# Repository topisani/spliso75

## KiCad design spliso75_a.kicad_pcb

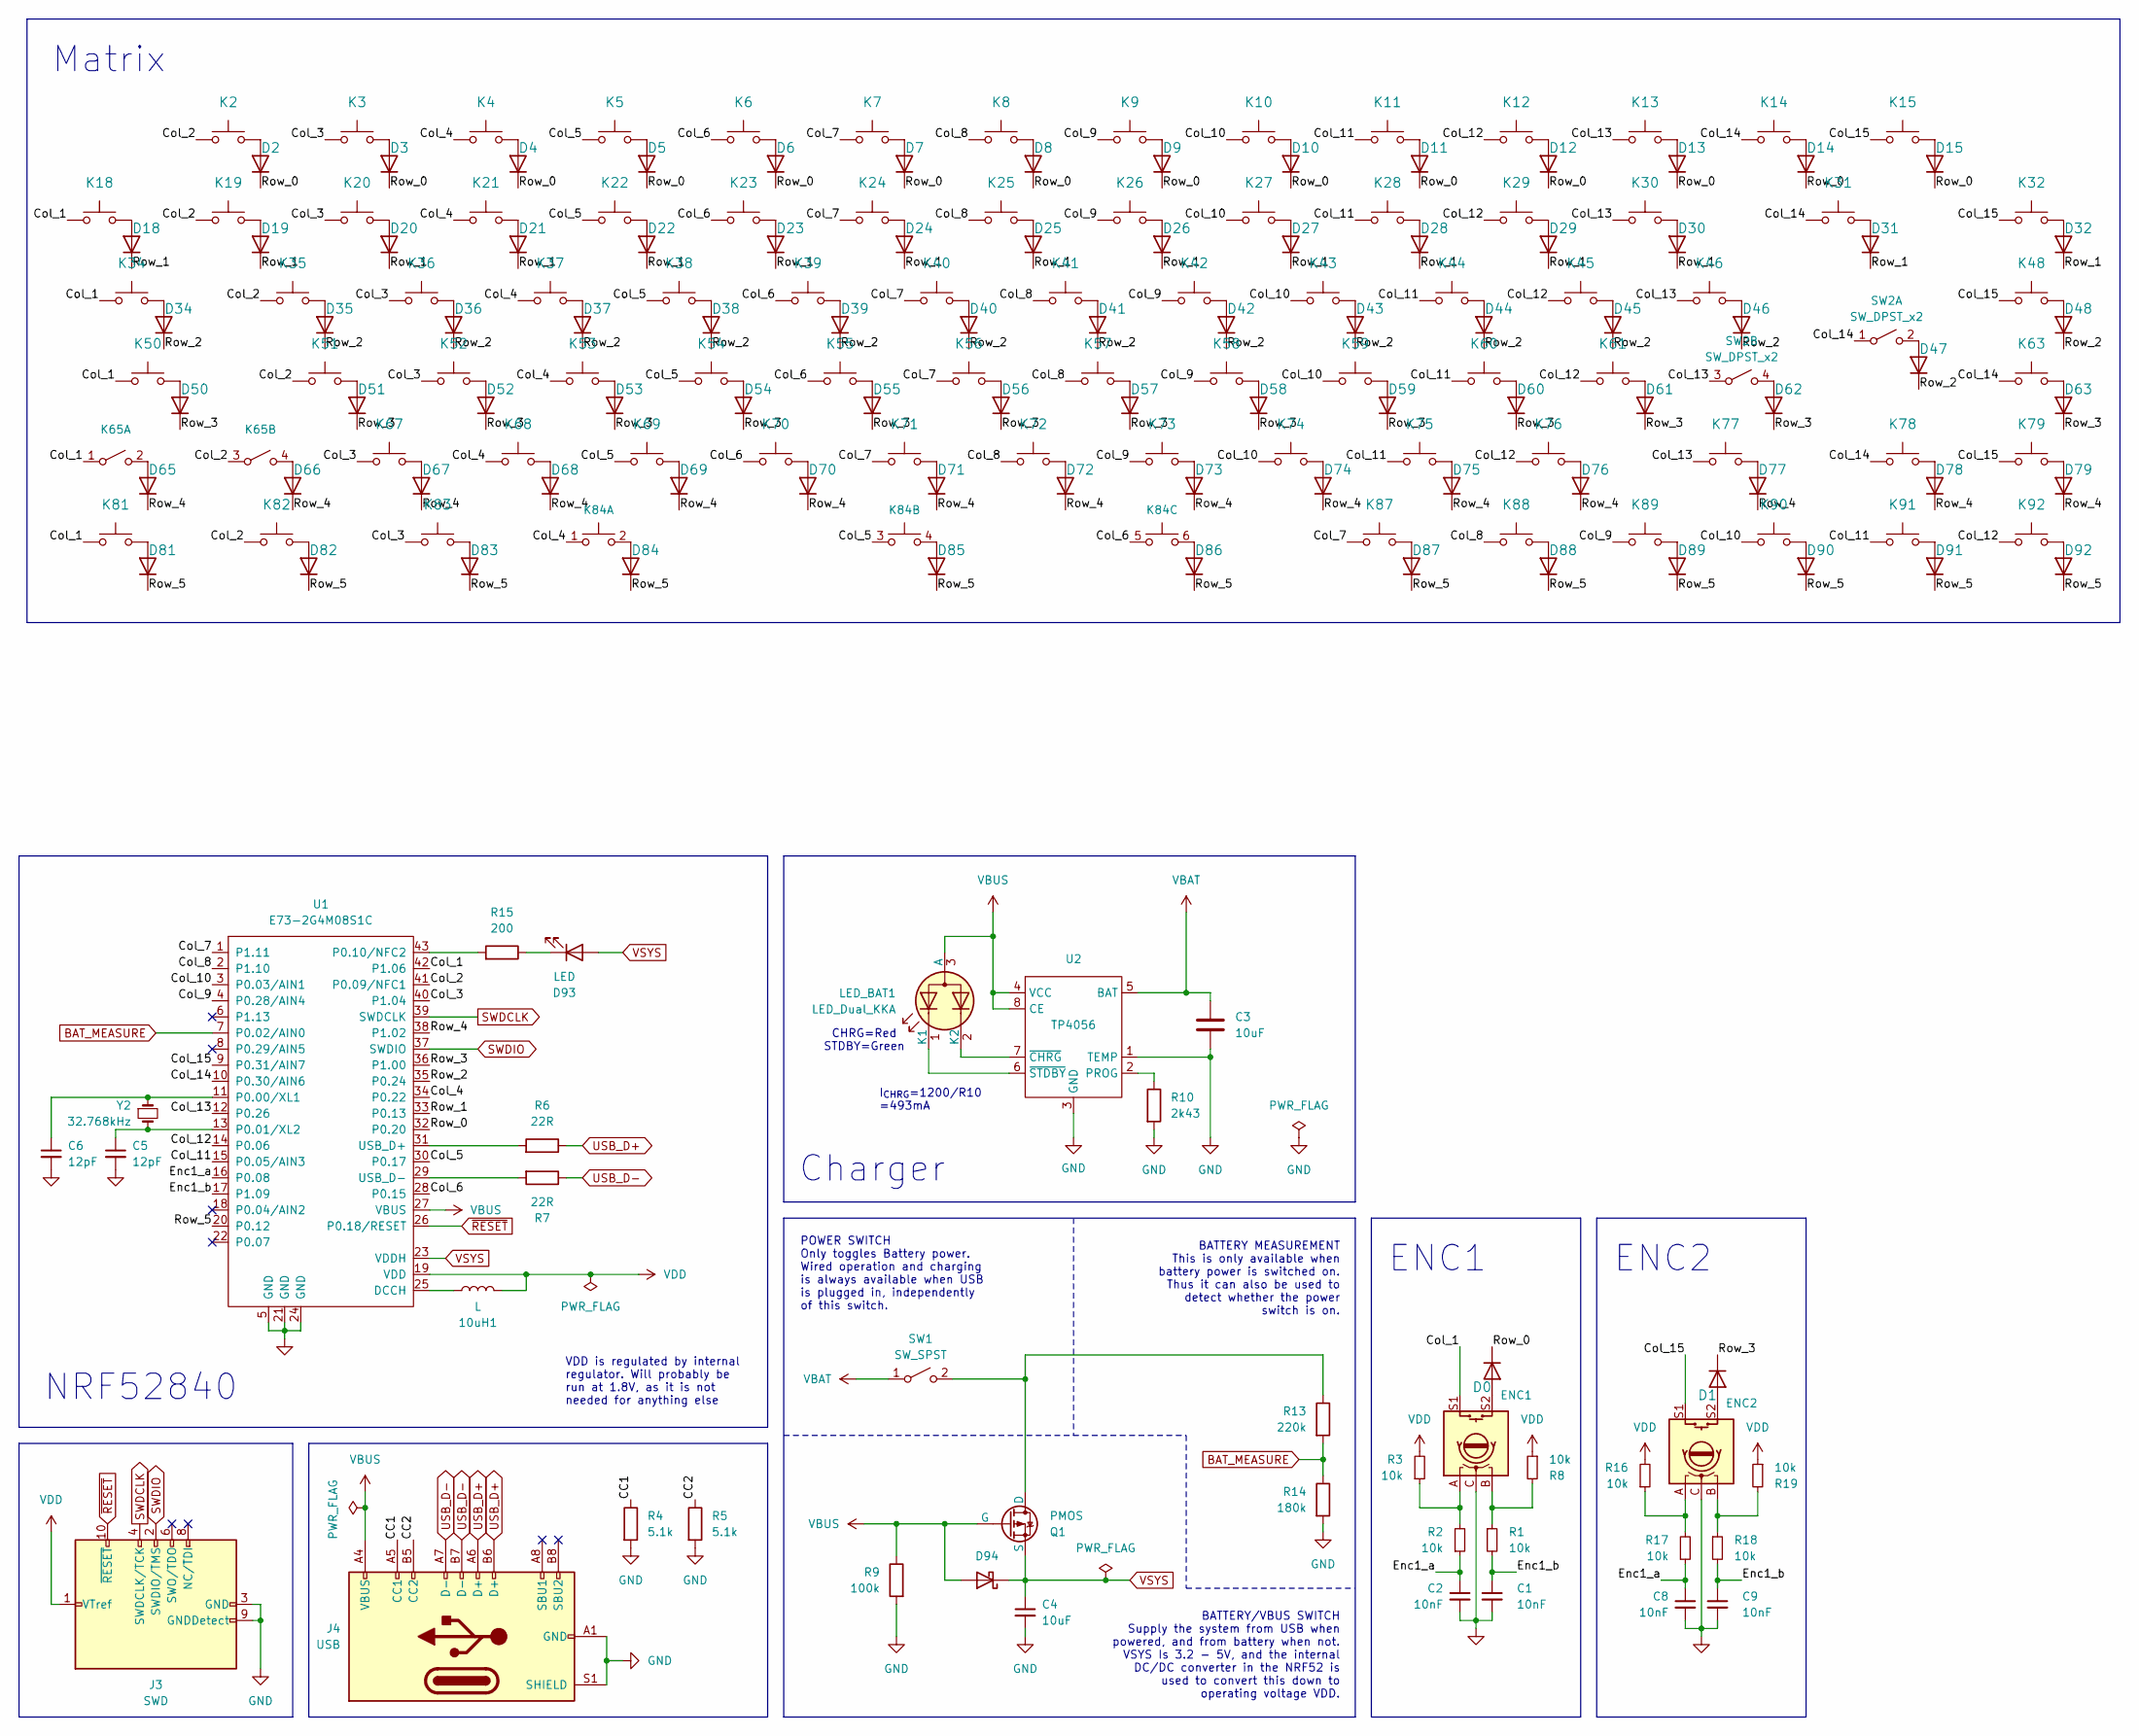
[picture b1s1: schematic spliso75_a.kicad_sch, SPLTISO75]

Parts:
10uH1: L; L_0805_2012Metric
C1, C2, C8, C9: 10nF; C_0603_1608Metric
C3, C4: 10uF; C_0603_1608Metric
C5, C6: 12pF; C_0603_1608Metric
D0, D1, D2, D3, D4, D5, D6, D7, D8, D9, D10, D11, D12, D13, D14, D15, D18, D19, D20, D21, D22, D23, D24, D25, D26, D27, D28, D29, D30, D31, D32, D34, D35, D36, D37, D38, D39, D40, D41, D42, D43, D44, D45, D46, D47, D48, D50, D51, D52, D53, D54, D55, D56, D57, D58, D59, D60, D61, D62, D63, D65, D66, D67, D68, D69, D70, D71, D72, D73, D74, D75, D76, D77, D78, D79, D81, D82, D83, D84, D85, D86, D87, D88, D89, D90, D91, D92: D; D_0805_2012Metric_Pad1.15x1.40mm_HandSolder
D93: LED; LED_0603_1608Metric_Pad1.05x0.95mm_HandSolder
D94: D_Schottky; D_0603_1608Metric
ENC1, ENC2: Encoder_Or_Switch
J3: SWD; PinHeader_2x05_P1.27mm_Vertical_SMD
J4: USB; USB_C_Receptacle_Molex_105450-0101
K2: F1; SW_Cherry_MX_1.00u_PCB
K3: F2; SW_Cherry_MX_1.00u_PCB
K4: F3; SW_Cherry_MX_1.00u_PCB
K5: F4; SW_Cherry_MX_1.00u_PCB
K6: F5; SW_Cherry_MX_1.00u_PCB
K7: F6; SW_Cherry_MX_1.00u_PCB
K8: F7; SW_Cherry_MX_1.00u_PCB
K9: F8; SW_Cherry_MX_1.00u_PCB
K10: F9; SW_Cherry_MX_1.00u_PCB
K11: F10; SW_Cherry_MX_1.00u_PCB
K12: F11; SW_Cherry_MX_1.00u_PCB
K13: F12; SW_Cherry_MX_1.00u_PCB
K14: Insert; SW_Cherry_MX_1.00u_PCB
K15: Delete; SW_Cherry_MX_1.00u_PCB
K18: Esc; SW_Cherry_MX_1.00u_PCB
K19: !,1; SW_Cherry_MX_1.00u_PCB
K20: ",2; SW_Cherry_MX_1.00u_PCB
K21: £,3; SW_Cherry_MX_1.00u_PCB
K22: $,4; SW_Cherry_MX_1.00u_PCB
K23: %,5; SW_Cherry_MX_1.00u_PCB
K24: ^,6; SW_Cherry_MX_1.00u_PCB
K25: &,7; SW_Cherry_MX_1.00u_PCB
K26: *,8; SW_Cherry_MX_1.00u_PCB
K27: (,9; SW_Cherry_MX_1.00u_PCB
K28: ),0; SW_Cherry_MX_1.00u_PCB
K29: _,-; SW_Cherry_MX_1.00u_PCB
K30: +,=; SW_Cherry_MX_1.00u_PCB
K31: Backspace; SW_Cherry_MX_2.00u_PCB
K32: PgUp; SW_Cherry_MX_1.00u_PCB
K34: Tab; SW_Cherry_MX_1.50u_PCB
K35: Q; SW_Cherry_MX_1.00u_PCB
K36: W; SW_Cherry_MX_1.00u_PCB
K37: E; SW_Cherry_MX_1.00u_PCB
K38: R; SW_Cherry_MX_1.00u_PCB
K39: T; SW_Cherry_MX_1.00u_PCB
K40: Y; SW_Cherry_MX_1.00u_PCB
K41: U; SW_Cherry_MX_1.00u_PCB
K42: I; SW_Cherry_MX_1.00u_PCB
K43: O; SW_Cherry_MX_1.00u_PCB
K44: P; SW_Cherry_MX_1.00u_PCB
K45: {,[; SW_Cherry_MX_1.00u_PCB
K46: },]; SW_Cherry_MX_1.00u_PCB
K48: PgDn; SW_Cherry_MX_1.00u_PCB
K50: Ctrl; SW_Cherry_MX_1.75u_PCB
K51: A; SW_Cherry_MX_1.00u_PCB
K52: S; SW_Cherry_MX_1.00u_PCB
K53: D; SW_Cherry_MX_1.00u_PCB
K54: F; SW_Cherry_MX_1.00u_PCB
K55: G; SW_Cherry_MX_1.00u_PCB
K56: H; SW_Cherry_MX_1.00u_PCB
K57: J; SW_Cherry_MX_1.00u_PCB
K58: K; SW_Cherry_MX_1.00u_PCB
K59: L; SW_Cherry_MX_1.00u_PCB
K60: :,;; SW_Cherry_MX_1.00u_PCB
K61: @,'; SW_Cherry_MX_1.00u_PCB
K63: Home; SW_Cherry_MX_1.00u_PCB
K65: SW_DPST_x2; ISOANSI_Shift
K67: Z; SW_Cherry_MX_1.00u_PCB
K68: X; SW_Cherry_MX_1.00u_PCB
K69: C; SW_Cherry_MX_1.00u_PCB
K70: V; SW_Cherry_MX_1.00u_PCB
K71: B; SW_Cherry_MX_1.00u_PCB
K72: N; SW_Cherry_MX_1.00u_PCB
K73: M; SW_Cherry_MX_1.00u_PCB
K74: <,,; SW_Cherry_MX_1.00u_PCB
K75: >,.; SW_Cherry_MX_1.00u_PCB
K76: ?,/; SW_Cherry_MX_1.00u_PCB
K77: Shift; SW_Cherry_MX_1.75u_PCB
K78: ↑; SW_Cherry_MX_1.00u_PCB
K79: End; SW_Cherry_MX_1.00u_PCB
K81: Ctrl; SW_Cherry_MX_1.25u_PCB
K82: Fn; SW_Cherry_MX_1.25u_PCB
K83: Win; SW_Cherry_MX_1.25u_PCB
K84: SW_Push_x3; SpaceGroup
K87: AltGr; SW_Cherry_MX_1.00u_PCB
K88: Win; SW_Cherry_MX_1.00u_PCB
K89: Menu; SW_Cherry_MX_1.00u_PCB
K90: ←; SW_Cherry_MX_1.00u_PCB
K91: ↓; SW_Cherry_MX_1.00u_PCB
K92: →; SW_Cherry_MX_1.00u_PCB
LED_BAT1: LED_Dual_KKA; SW_Cherry_MX_1.25u_PCB
Q1: PMOS; SOT-23-3
R1, R2, R3, R8, R16, R17, R18, R19: 10k; R_0402_1005Metric
R4, R5: 5.1k; R_0402_1005Metric
R6, R7: 22R; R_0402_1005Metric
R9: 100k; R_0402_1005Metric
R10: 2k43; R_0402_1005Metric
R13: 220k; R_0402_1005Metric
R14: 180k; R_0402_1005Metric
R15: 200; R_0402_1005Metric
SW1: SW_SPST; SOT-23-3
SW2: SW_DPST_x2; SW_Cherry_MX_ISOANSIEnter_PCB
U1: E73-2G4M08S1C; E73-2G4M08S1C-52840
U2: TP4056; SOP-8-1EP_4.57x4.57mm_P1.27mm_EP4.57x4.45mm
Y2: 32.768kHz; Crystal_SMD_0603-2Pin_6.0x3.5mm

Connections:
/CC1: J4.A5 (CC1), R4.1
/CC2: J4.B5 (CC2), R5.1
/Col_1: ENC1.S1, K18.1, K34.1, K50.1, K65.1 (A), K81.1, U1.42 (P1.06)
/Col_2: K2.1, K19.1, K35.1, K51.1, K65.3 (A), K82.1, U1.41 (P0.09/NFC1)
/Col_3: K3.1, K20.1, K36.1, K52.1, K67.1, K83.1, U1.40 (P1.04)
/Col_4: K4.1, K21.1, K37.1, K53.1, K68.1, K84.1 (C), U1.34 (P0.22)
/Col_5: K5.1, K22.1, K38.1, K54.1, K69.1, K84.3 (C), U1.30 (P0.17)
/Col_6: K6.1, K23.1, K39.1, K55.1, K70.1, K84.5 (C), U1.28 (P0.15)
/Col_7: K7.1, K24.1, K40.1, K56.1, K71.1, K87.1, U1.1 (P1.11)
/Col_8: K8.1, K25.1, K41.1, K57.1, K72.1, K88.1, U1.2 (P1.10)
/Col_9: K9.1, K26.1, K42.1, K58.1, K73.1, K89.1, U1.4 (P0.28/AIN4)
/Col_10: K10.1, K27.1, K43.1, K59.1, K74.1, K90.1, U1.3 (P0.03/AIN1)
/Col_11: K11.1, K28.1, K44.1, K60.1, K75.1, K91.1, U1.15 (P0.05/AIN3)
/Col_12: K12.1, K29.1, K45.1, K61.1, K76.1, K92.1, U1.14 (P0.06)
/Col_13: K13.1, K30.1, K46.1, K77.1, SW2.3 (A), U1.12 (P0.26)
/Col_14: K14.1, K31.1, K63.1, K78.1, SW2.1 (A), U1.10 (P0.30/AIN6)
/Col_15: ENC2.S1, K15.1, K32.1, K48.1, K79.1, U1.9 (P0.31/AIN7)
/Enc1_a: C2.1, C8.1, R2.1, R17.1, U1.16 (P0.08)
/Enc1_b: C1.1, C9.1, R1.2, R18.2, U1.17 (P1.09)
/Row_0: D0.1 (K), D2.1 (K), D3.1 (K), D4.1 (K), D5.1 (K), D6.1 (K), D7.1 (K), D8.1 (K), D9.1 (K), D10.1 (K), D11.1 (K), D12.1 (K), D13.1 (K), D14.1 (K), D15.1 (K), U1.32 (P0.20)
/Row_1: D18.1 (K), D19.1 (K), D20.1 (K), D21.1 (K), D22.1 (K), D23.1 (K), D24.1 (K), D25.1 (K), D26.1 (K), D27.1 (K), D28.1 (K), D29.1 (K), D30.1 (K), D31.1 (K), D32.1 (K), U1.33 (P0.13)
/Row_2: D34.1 (K), D35.1 (K), D36.1 (K), D37.1 (K), D38.1 (K), D39.1 (K), D40.1 (K), D41.1 (K), D42.1 (K), D43.1 (K), D44.1 (K), D45.1 (K), D46.1 (K), D47.1 (K), D48.1 (K), U1.35 (P0.24)
/Row_3: D1.1 (K), D50.1 (K), D51.1 (K), D52.1 (K), D53.1 (K), D54.1 (K), D55.1 (K), D56.1 (K), D57.1 (K), D58.1 (K), D59.1 (K), D60.1 (K), D61.1 (K), D62.1 (K), D63.1 (K), U1.36 (P1.00)
/Row_4: D65.1 (K), D66.1 (K), D67.1 (K), D68.1 (K), D69.1 (K), D70.1 (K), D71.1 (K), D72.1 (K), D73.1 (K), D74.1 (K), D75.1 (K), D76.1 (K), D77.1 (K), D78.1 (K), D79.1 (K), U1.38 (P1.02)
/Row_5: D81.1 (K), D82.1 (K), D83.1 (K), D84.1 (K), D85.1 (K), D86.1 (K), D87.1 (K), D88.1 (K), D89.1 (K), D90.1 (K), D91.1 (K), D92.1 (K), U1.20 (P0.12)
BAT_MEASURE: R13.2, R14.1, U1.7 (P0.02/AIN0)
GND: C1.2, C2.2, C3.2, C4.2, C5.2, C6.2, C8.2, C9.2, ENC1.C, ENC2.C, J3.3 (GND), J3.5 (GND), J3.9 (GNDDetect), J4.A1 (GND), J4.A12 (GND), J4.B1 (GND), J4.B12 (GND), J4.S1 (SHIELD), R4.2, R5.2, R9.2, R10.2, R14.2, U1.5 (GND), U1.21 (GND), U1.24 (GND), U2.1 (TEMP), U2.3 (GND)
unnamed: D0.2 (A), ENC1.S2
unnamed: D1.2 (A), ENC2.S2
unnamed: D2.2 (A), K2.2
unnamed: D3.2 (A), K3.2
unnamed: D4.2 (A), K4.2
unnamed: D5.2 (A), K5.2
unnamed: D6.2 (A), K6.2
unnamed: D7.2 (A), K7.2
unnamed: D8.2 (A), K8.2
unnamed: D9.2 (A), K9.2
unnamed: D10.2 (A), K10.2
unnamed: D11.2 (A), K11.2
unnamed: D12.2 (A), K12.2
unnamed: D13.2 (A), K13.2
unnamed: D14.2 (A), K14.2
unnamed: D15.2 (A), K15.2
unnamed: D18.2 (A), K18.2
unnamed: D19.2 (A), K19.2
unnamed: D20.2 (A), K20.2
unnamed: D21.2 (A), K21.2
unnamed: D22.2 (A), K22.2
unnamed: D23.2 (A), K23.2
unnamed: D24.2 (A), K24.2
unnamed: D25.2 (A), K25.2
unnamed: D26.2 (A), K26.2
unnamed: D27.2 (A), K27.2
unnamed: D28.2 (A), K28.2
unnamed: D29.2 (A), K29.2
unnamed: D30.2 (A), K30.2
unnamed: D31.2 (A), K31.2
unnamed: D32.2 (A), K32.2
unnamed: D34.2 (A), K34.2
unnamed: D35.2 (A), K35.2
unnamed: D36.2 (A), K36.2
unnamed: D37.2 (A), K37.2
unnamed: D38.2 (A), K38.2
unnamed: D39.2 (A), K39.2
unnamed: D40.2 (A), K40.2
unnamed: D41.2 (A), K41.2
unnamed: D42.2 (A), K42.2
unnamed: D43.2 (A), K43.2
unnamed: D44.2 (A), K44.2
unnamed: D45.2 (A), K45.2
unnamed: D46.2 (A), K46.2
unnamed: D47.2 (A), SW2.2 (B)
unnamed: D48.2 (A), K48.2
unnamed: D50.2 (A), K50.2
unnamed: D51.2 (A), K51.2
unnamed: D52.2 (A), K52.2
unnamed: D53.2 (A), K53.2
unnamed: D54.2 (A), K54.2
unnamed: D55.2 (A), K55.2
unnamed: D56.2 (A), K56.2
unnamed: D57.2 (A), K57.2
unnamed: D58.2 (A), K58.2
unnamed: D59.2 (A), K59.2
unnamed: D60.2 (A), K60.2
unnamed: D61.2 (A), K61.2
unnamed: D62.2 (A), SW2.4 (B)
unnamed: D63.2 (A), K63.2
unnamed: D65.2 (A), K65.2 (B)
unnamed: D66.2 (A), K65.4 (B)
unnamed: D67.2 (A), K67.2
unnamed: D68.2 (A), K68.2
unnamed: D69.2 (A), K69.2
unnamed: D70.2 (A), K70.2
unnamed: D71.2 (A), K71.2
unnamed: D72.2 (A), K72.2
unnamed: D73.2 (A), K73.2
unnamed: D74.2 (A), K74.2
unnamed: D75.2 (A), K75.2
unnamed: D76.2 (A), K76.2
unnamed: D77.2 (A), K77.2
unnamed: D78.2 (A), K78.2
unnamed: D79.2 (A), K79.2
unnamed: D81.2 (A), K81.2
unnamed: D82.2 (A), K82.2
unnamed: D83.2 (A), K83.2
unnamed: D84.2 (A), K84.2 (D)
unnamed: D85.2 (A), K84.4 (D)
unnamed: D86.2 (A), K84.6 (D)
unnamed: D87.2 (A), K87.2
unnamed: D88.2 (A), K88.2
unnamed: D89.2 (A), K89.2
unnamed: D90.2 (A), K90.2
unnamed: D91.2 (A), K91.2
unnamed: D92.2 (A), K92.2
unnamed: D93.1 (K), R15.1
unnamed: ENC1.A, R2.2, R3.1
unnamed: ENC1.B, R1.1, R8.2
unnamed: ENC2.A, R16.1, R17.2
unnamed: ENC2.B, R18.1, R19.2
unnamed: LED_BAT1.1 (K1), U2.6 (~STDBY)
unnamed: LED_BAT1.2 (K2), U2.7 (~CHRG)
unnamed: Q1.1 (D), R13.1, SW1.2 (B)
unnamed: 10uH1.1, U1.25 (DCCH)
unnamed: C6.1, U1.11 (P0.00/XL1), Y2.1
unnamed: C5.1, U1.13 (P0.01/XL2), Y2.2
unnamed: R15.2, U1.43 (P0.10/NFC2)
unnamed: R6.2, U1.31 (USB_D+)
unnamed: R7.2, U1.29 (USB_D-)
unnamed: R10.1, U2.2 (PROG)
SWDCLK: J3.4 (SWDCLK/TCK), U1.39 (SWDCLK)
SWDIO: J3.2 (SWDIO/TMS), U1.37 (SWDIO)
USB_D+: J4.A6 (D+), J4.B6 (D+), R6.1
USB_D-: J4.A7 (D-), J4.B7 (D-), R7.1
VBAT: C3.1, SW1.1 (A), U2.5 (BAT)
VBUS: D94.2 (A), J4.A4 (VBUS), J4.A9 (VBUS), J4.B4 (VBUS), J4.B9 (VBUS), LED_BAT1.3 (A), Q1.2 (G), R9.1, U1.27 (VBUS), U2.4 (VCC), U2.8 (CE)
VDD: 10uH1.2, J3.1 (VTref), R3.2, R8.1, R16.2, R19.1, U1.19 (VDD)
VSYS: C4.1, D93.2 (A), D94.1 (K), Q1.3 (S), U1.23 (VDDH)
~RESET: J3.10 (~RESET), U1.26 (P0.18/RESET)

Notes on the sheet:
VDD is regulated by internal regulator. Will probably be run at 1.8V, as it is not needed for anything else
BATTERY/VBUS SWITCH Supply the system from USB when powered, and from battery when not. VSYS Is 3.2 - 5V, and the internal DC/DC converter in the NRF52 is used to convert this down to operating voltage VDD.
I_{CHRG}=1200/R10 =493mA
BATTERY MEASUREMENT This is only available when battery power is switched on. Thus it can also be used to detect whether the power switch is on.
POWER SWITCH Only toggles Battery power. Wired operation and charging is always available when USB is plugged in, independently of this switch.
NRF52840
Charger
CHRG=Red STDBY=Green
Matrix
ENC1
ENC2

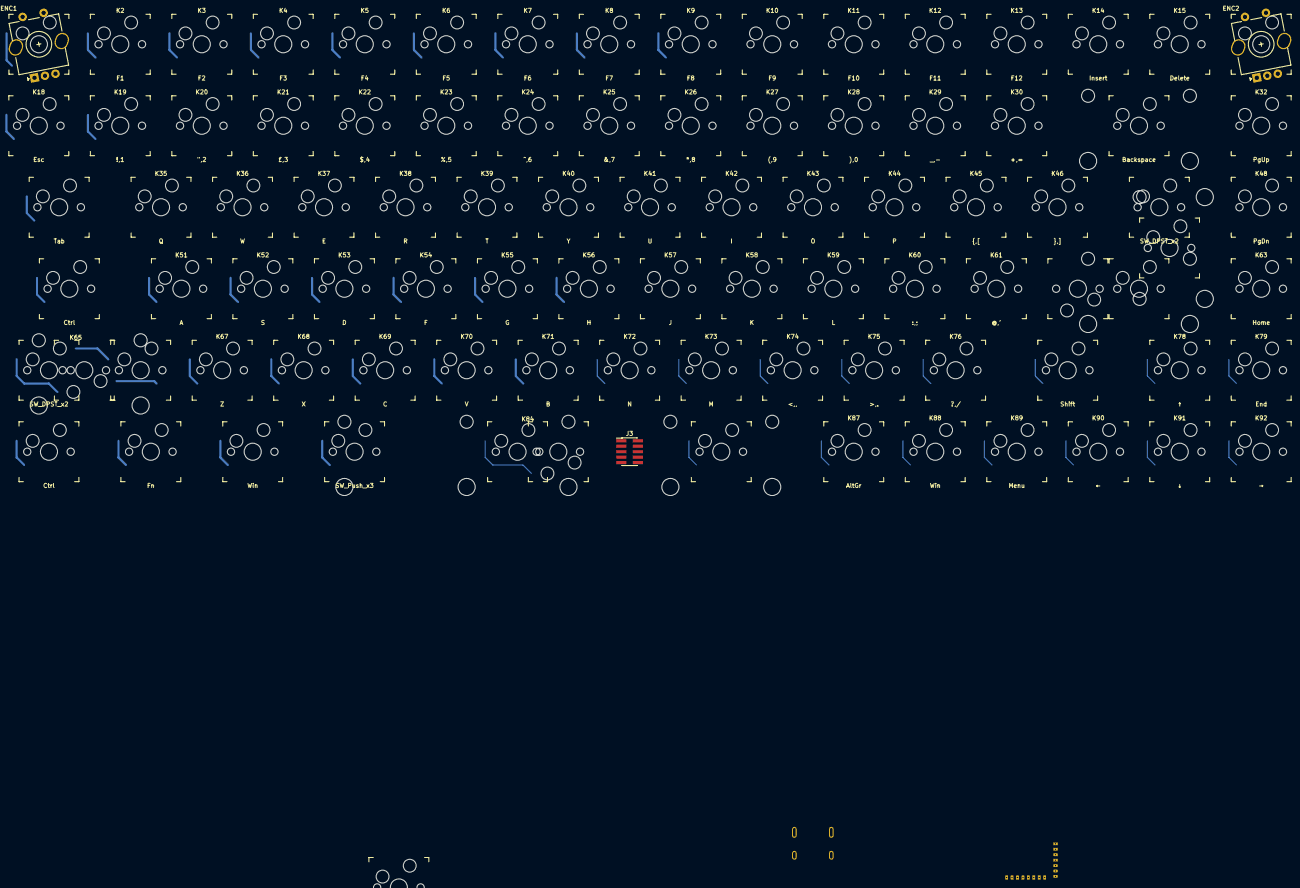
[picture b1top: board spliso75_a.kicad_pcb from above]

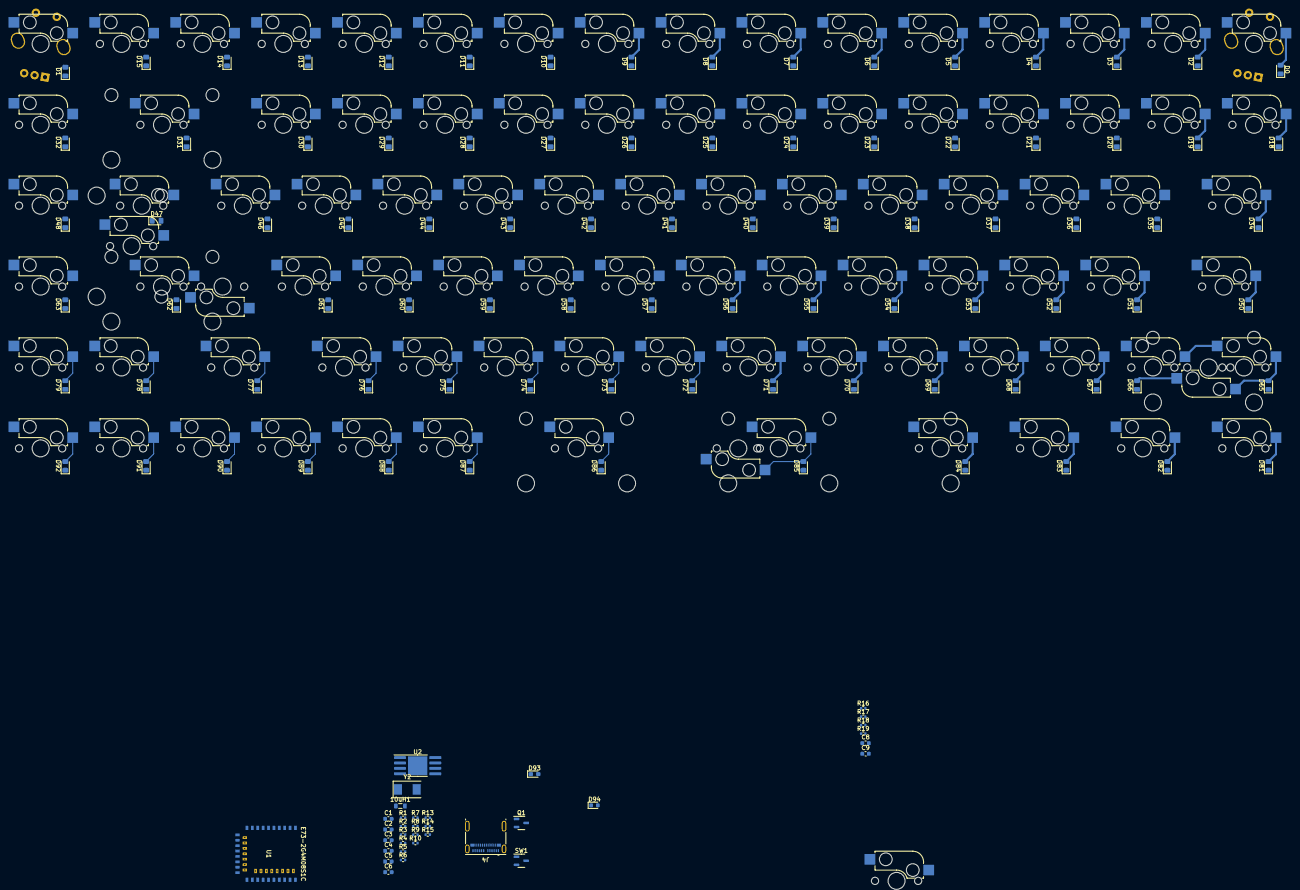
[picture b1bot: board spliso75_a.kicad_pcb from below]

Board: 2 copper layers, 206 parts (121 on the bottom side), 138 nets.
